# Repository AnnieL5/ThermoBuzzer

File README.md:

## ThermoBuzzer, a Thermosenser to Prevent Over Boiled Pots. 

### What it is
This device integrates a thermosensor, buzzer, and a button, and can make alarms when the temperature (the steam it detects) reaches a certain threshold. 

### Motivation / Inspiration / Problem

One Saturday afternoon my father left the stove, with the water heating up, for almost half an hour until the pot boiled dry and the fire alarm turned on, simply because he forgot the fact that the stove is still on. That moment inspired me to make a change - to build a device that could sense the temperature and alarm people that the burner is still active. 

### How to use it

1. Solder the electrical parts (see BOM) onto the PCB. Insert the PCB into the case and secure using m3 self-tapping screws

2. Insert the battery to start the machine. Slide in the lid and secure using a m3 self-tapping screw

3. Place it near the stoves. 

    Once the temperature continuously reaches 50 degrees (able to modify using a constant), ThermoBuzzer will beep continuously every five minutes until the button is clicked to ensure someone is there.

    Once the temperature reaches 70 degrees (able to modify using a constant), ThermoBuzzer will beep continuously right away until the button is clicked.

4. (Optional) To adjust the temperature threshold, take out the pcb from the case, modify amd reupload the program to the arduino pro mini.

### Code Example
Go checkout the example code in firmware/thermobuzzer.imo and upload it onto the arduino pro mini

For how to upload code onto arduino pro mini using arduino uno, check out 
https://www.instructables.com/How-to-Program-Arduino-Pro-Mini-Using-Arduino-UNO/

### Image of the entire cad / Finished product

### Image of the entire cad (with lid) / Finished product

### Image of the final PCB

### Image of the wiring schematic

## Zine page

## Demo Video

https://youtu.be/lv5Z6S4dAAs

## Product Design

### CAD dimensions
Side + top + base thickness: 2mm
supporting bar: r=4mm, h=4mm
Case height: 2mm base + 4mm supporting bar + 1.6mm board + 15.1mm battery height + 2mm flex + 2mm top

### Circuit Diagram 

### Sub-circuit Description
Diagrams from www.circuitbasics.com. 
#### Temperature sensor (NTC MF11) and Arduino

NTC MF11
The value of the resistor should be roughly equal to the resistance of the thermistor.

#### BME280
Reference links:

BME280
https://randomnerdtutorials.com/bme280-sensor-arduino-pressure-temperature-humidity/

https://docs.cirkitdesigner.com/component/3d8e6da8-841a-47a6-a1aa-0aa902c905e1/aht20bmp280

Code: https://randomnerdtutorials.com/bme280-sensor-arduino-pressure-temperature-humidity/

Arduino Library: adafruit bme280

It supports SPI or I2C communication

| BME280 |	Arduino |
|--|--|
|Vin | 	5V |
|GND |	GND |
|SCL |	A5 |
|SDA |	A4 |

| BME280 |	Arduino |
|--|--|
|SCK (SPI Clock)|	Pin 13|
|SDO (MISO)|	Pin 12|
|SDI (MOSI)|	Pin 11|
|CS (Chip Select)|	Pin 10|

#### Buzzer, Button and Arduino

## Requirements (Need future work)
| Req # | Requirements |
|---|---|
| 1.1 | The thermosensor shall be able to measure the temperature accurately for further actions|
| 1.2 | The thermosensor shall be able to beep when the temperature reaches a certain threshold |
| 1.3 | The button should be able to stop the buzzer from beeping |
| 1.4 | The temperature threshold should be adjustable by the user |

## Bill of Materials (BOM)
| Product name          | Product Description                          | Amount | Unit Price | Shipping Fee | Total Price | Link                                                                                                                                                                                                                                                                                                                                                                                                                                                                                                                                                                                                                                  |
| --------------------- | -------------------------------------------- | ------ | ---------- | ------------ | ----------- | ------------------------------------------------------------------------------------------------------------------------------------------------------------------------------------------------------------------------------------------------------------------------------------------------------------------------------------------------------------------------------------------------------------------------------------------------------------------------------------------------------------------------------------------------------------------------------------------------------------------------------------- |
| Arduino Pro Mini,      | ÊATMEGA328P 3.3V 8MHz                        | 1      | $6.14      |              | $6.14       | https://www.aliexpress.com/item/1005009384358010.html?spm=a2g0o.detail.0.0.3d69kxh4kxh4TT&mp=1&pdp_npi=6%40dis%21CAD%21CAD+12.34%21CAD+6.19%21%21CAD+6.19%21%21%21%402101e2b217772431183538792e7ffd%2112000048937356319%21ct%21CA%216218818596%21%211%210%21                                                                                                                                                                                                                                                                                                                                                                          |
| Temperature Sensor,    | AHT20+BMP280                                 | 1      | $4.59      |              | $4.59       | https://www.aliexpress.com/item/1005005982427374.html?spm=a2g0o.detail.0.0.91dbOMYjOMYjR3&mp=1&sourceType=570&pdp_npi=6%40dis%21CAD%21CAD+7.57%21CAD+4.59%21%21CAD+4.59%21%21%21%402101d6ff17773442520382830e94da%2112000035166631251%21ct%21CA%216218818596%21%211%210%21&pdp_ext_f=%7B%22cart2PdpParams%22%3A%7B%22sourceType%22%3A%22570%22%2C%22cartSource%22%3A%22main%22%7D%7D                                                                                                                                                                                                                                                  |
| Thermisor,             | 10PCS NTC ThermistorÊMF52 NTC-MF52AT         | 1      | 3.46       |              | $3.46       | https://www.aliexpress.com/item/1005007016386078.html?spm=a2g0o.detail.0.0.177fzTz7zTz79e&mp=1&pdp_npi=6%40dis%21CAD%21CAD+7.07%21CAD+3.46%21%21CAD+3.46%21%21%21%402101d6ff17773445233621202e94da%2112000039082044667%21ct%21CA%216218818596%21%211%210%21                                                                                                                                                                                                                                                                                                                                                                           |
| Passive Buzzer,        | 10PCS Passive Buzzer Kits 12085              | 1      | 2.79       |              | $2.79       | https://www.aliexpress.com/item/1005007038458518.html?spm=a2g0o.detail.0.0.291d6UQD6UQDcn&mp=1&sourceType=570&pdp_npi=6%40dis%21CAD%21CAD+7.56%21CAD+3.09%21%21CAD+3.09%21%21%21%402101d6ff17773446457813771e94da%2112000039180355191%21ct%21CA%216218818596%21%211%210%21&pdp_ext_f=%7B%22cart2PdpParams%22%3A%7B%22sourceType%22%3A%22570%22%2C%22cartSource%22%3A%22main%22%7D%7D                                                                                                                                                                                                                                                  |
| Buttons,               | 6\*6\*10mm 20pics                            | 1      | 2.29       |              | $2.29       | https://www.aliexpress.com/item/1005006046180384.html?spm=a2g0o.cart.0.0.31e138dackOqlz&mp=1&pdp_npi=6%40dis%21CAD%21CAD+2.29%21CAD+2.29%21%21CAD+2.29%21%21%21%402103119c17773470443845760e9623%2112000035472972539%21ct%21CA%216218818596%21%211%210%21                                                                                                                                                                                                                                                                                                                                                                             |
| AA Battery,            | 1                                            | NA     |            |              |             |
| THT Battery Holder    | 14500 Battery Box With Pins 1AA 1.5V         | 1      | 0.33       | 7.48         | $7.81       | https://www.aliexpress.com/item/1005005620966310.html?spm=a2g0o.cart.0.0.358a38dadNcuNR&mp=1&pdp_npi=6%40dis%21CAD%21CAD+0.38%21CAD+0.32%21%21CAD+0.32%21%21%21%402101eee917774109006605329ec0dc%2112000033776650718%21ct%21CA%216218818596%21%215%210%21                                                                                                                                                                                                                                                                                                                                                                             |
| Voltage Regulator,     | 0.8V-5V to 3V 3.3V 5V Boost Voltage Regulate | 1      | 3.85       |              | $3.85       | https://www.aliexpress.com/item/1005006167931077.html?spm=a2g0o.detail.0.0.4a7cjdtRjdtRpQ&mp=1&pdp_npi=6%40dis%21CAD%21CAD+3.96%21CAD+3.86%21%21CAD+3.86%21%21%21%402101d6ff17773444964128610e94da%2112000036084126229%21ct%21CA%216218818596%21%211%210%21                                                                                                                                                                                                                                                                                                                                                                           |
| m3 self-tapping screw, | ZONSANTA M3x50pc 5mm                         | 1      | 2.79       |              | $2.79       | https://www.aliexpress.com/item/4000982209705.html?spm=a2g0o.productlist.main.2.5e0a5049GO2c6k&algo_pvid=d9d1041d-5b82-4d1d-adb8-2c50ae22e721&algo_exp_id=d9d1041d-5b82-4d1d-adb8-2c50ae22e721-1&pdp_ext_f=%7B%22order%22%3A%2214058%22%2C%22eval%22%3A%221%22%2C%22fromPage%22%3A%22search%22%7D&pdp_npi=6%40dis%21CAD%212.04%211.99%21%21%211.46%211.42%21%40210328d417774091351247794e1c13%2110000013191635027%21sea%21CA%216218818596%21X%211%210%21n_tag%3A-29919%3Bd%3A26a99932%3Bm03_new_user%3A-29895&curPageLogUid=Y5TAugc4ns7L&utparam-url=scene%3Asearch%7Cquery_from%3A%7Cx_object_id%3A4000982209705%7C_p_origin_prod%3A |
| resistor,              | 100k                                         | 1      | 0          |              | $0.00       |                                                                                                                                                                                                                                                                                                                                                                                                                                                                                                                                                                                                                                       |
| resistor,              | 10k                                          | 1      | 0          |              | $0.00       |                                                                                                                                                                                                                                                                                                                                                                                                                                                                                                                                                                                                                                       |
| head pins,             | 5 male 5 female                              | 1      | 5.19       |              | $5.19       | https://www.aliexpress.com/item/1005007235591794.html?spm=a2g0o.cart.0.0.31e138dackOqlz&mp=1&sourceType=570&pdp_npi=6%40dis%21CAD%21CAD+16.72%21CAD+5.19%21%21CAD+5.19%21%21%21%402103119c17773470443845760e9623%2112000039908542823%21ct%21CA%216218818596%21%211%210%21&pdp_ext_f=%7B%22cart2PdpParams%22%3A%7B%22sourceType%22%3A%22570%22%2C%22cartSource%22%3A%22main%22%7D%7D                                                                                                                                                                                                                                                   |
| Total                 |                                              |        |            |              | $38.91      |                                                                                                                                                                                                                                                                                                                                                                                                                                                                                                                                                                                                                                       |

### Thanks for checking it out!
Any questions or thoughts, feel free to reach out to atianyi.liang@gmail.com.

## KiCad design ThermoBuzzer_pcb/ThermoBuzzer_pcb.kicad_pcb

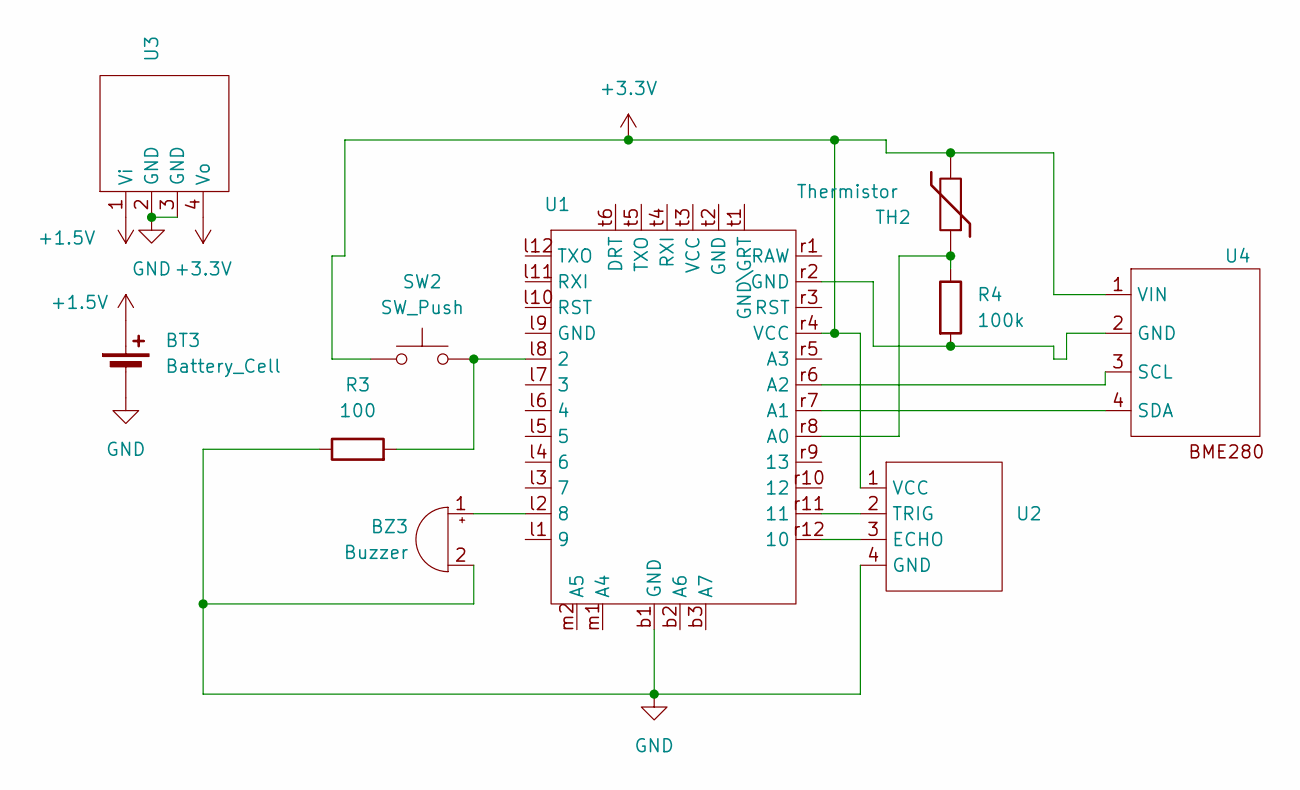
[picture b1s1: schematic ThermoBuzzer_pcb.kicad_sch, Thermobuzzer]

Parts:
BT3: Battery_Cell; BatteryHolder_Keystone_2460_1xAA
BZ3: Buzzer; Buzzer_12x9.5RM7.6
R3: 100; R_Axial_DIN0207_L6.3mm_D2.5mm_P7.62mm_Horizontal
R4: 100k; R_Axial_DIN0207_L6.3mm_D2.5mm_P7.62mm_Horizontal
SW2: SW_Push; SW_PUSH_6mm
TH2: Thermistor; R_Axial_DIN0207_L6.3mm_D2.5mm_P7.62mm_Horizontal
U1: arduino_pro_mini_new
U2: Ultrasonic Sensor HC-SR04
U3: ND0205MA Voltage Regulator
U4: AHT20+BMP280

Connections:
+1.5V: BT3.1 (+), U3.1 (Vi)
+3.3V: SW2.1, TH2.2, U1.r4 (VCC), U2.1 (VCC), U3.4 (Vo), U4.1 (VIN)
GND: BT3.2 (-), BZ3.2 (-), R3.1, U1.b1 (GND), U2.4 (GND), U3.2 (GND), U3.3 (GND)
unnamed: BZ3.1 (+), U1.l2 (8)
unnamed: R3.2, SW2.2, U1.l8 (2)
unnamed: U1.r12 (10), U2.3 (ECHO)
unnamed: U1.r11 (11), U2.2 (TRIG)
unnamed: R4.1, TH2.1, U1.r8 (A0)
unnamed: U1.r7 (A1), U4.4 (SDA)
unnamed: U1.r6 (A2), U4.3 (SCL)
unnamed: R4.2, U1.r2 (GND), U4.2 (GND)

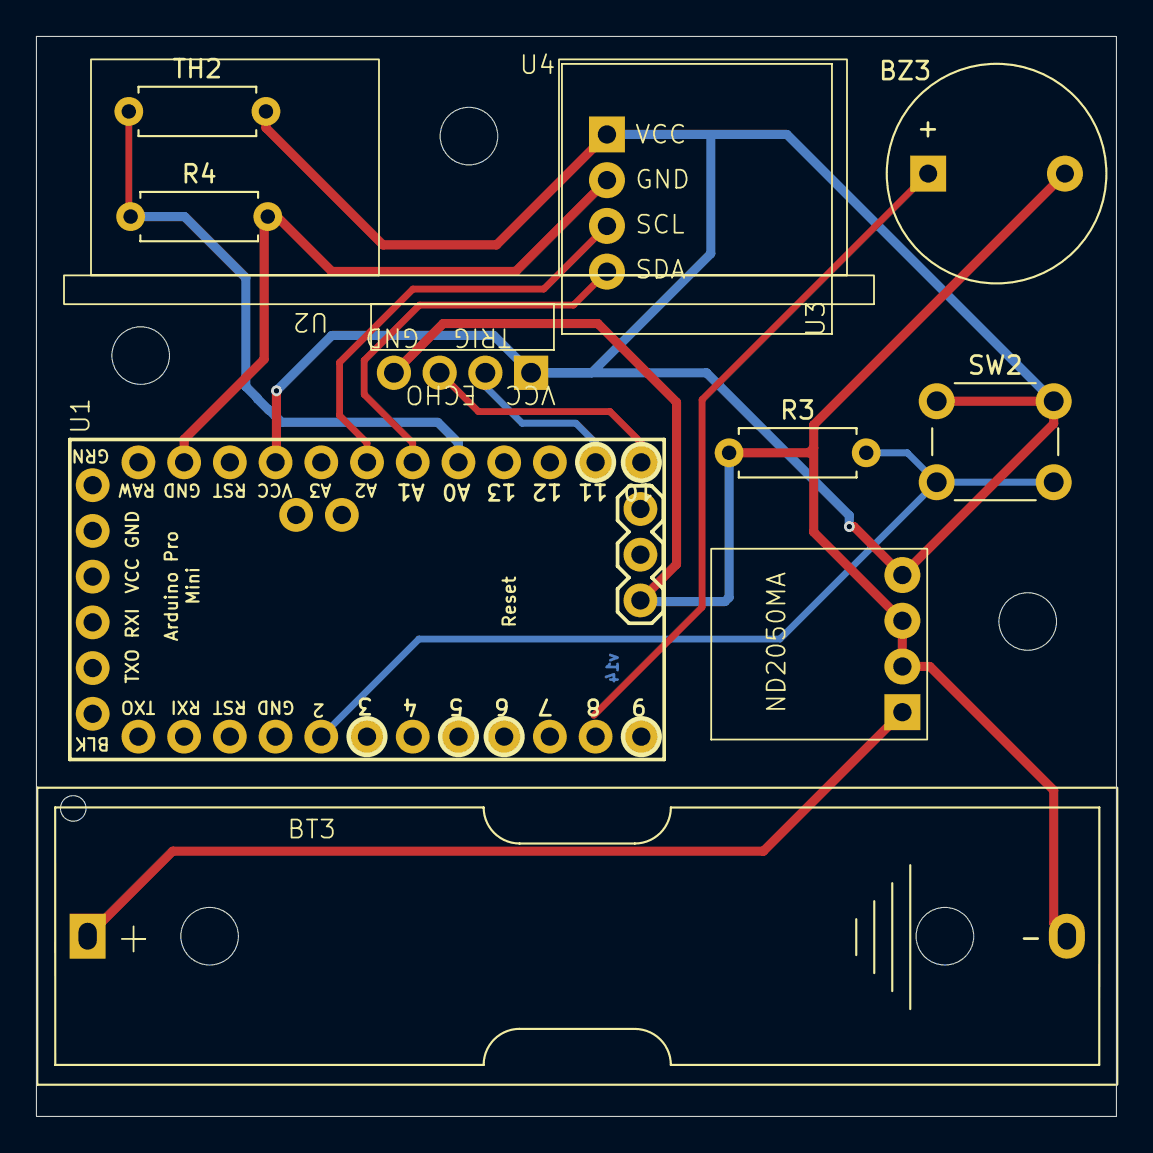
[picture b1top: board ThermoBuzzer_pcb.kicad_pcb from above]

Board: 2 copper layers, 60.0 x 60.0 mm, 10 parts (0 on the bottom side), 11 nets.

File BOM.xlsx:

BOM
Part Name | Type | Reference Designator | Quantity | Price | Link | Price | Notes
Temperature Sensor | NTC MF11, AHT20+BMP280 |  | 1 | 2.19 | AHT20+BMP280 Temperature Humidity Air Pressure Module High-precision Digital Te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 |  | https://www.aliexpress.com/ssr/300000512/BundleDeals2?spm=a2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 | https://www.amazon.ca/ANALOG-DEVICES-TMP36-Temperature-Senso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
Active Buzzer | 5V |  | 1 | 3.99 | https://www.aliexpress.com/w/wholesale-active-buzzer.html?g=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
Button |  |  | 1 | NA | https://www.aliexpress.com/w/wholesale-button-electronics.ht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
Resistor
Capacitor |  |  | 1 |  | https://www.aliexpress.com/w/wholesale-capacitor.html?g=y&Se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
Arduino | Arduino Nano (type) |  | 1 | 2.6 | https://www.aliexpress.com/item/1005004904865598.html?spm=a2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
 | Arduino pro mini |  |  | 6.19 | 1PCS Pro mini Atmega328 Pro Mini 328 Mini ATMEGA328P 3.3V 8MHz 5V 16Mhz for Ard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
Battery | 9v dc |  |  | 9.98 | https://www.amazon.ca/Duracell-Coppertop-Long-lasting-All-Pu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
Battery socket
Boost voltage regulator |  |  |  | 3.3 | Mini 0.8V-5V to 3V 3.3V 5V Boost Voltage Regulate Board Low-Power-Consumption H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
Product name | Product Description | Amount | Unit Price | Shipping Fee | Total Price | Link
Arduino Pro Mini | ATMEGA328P 3.3V 8MHz | 1 | 6.14 |  | 6.14 | https://www.aliexpress.com/item/1005009384358010.html?spm=a2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
Temperature Sensor | AHT20+BMP280 | 1 | 4.59 |  | 4.59 | https://www.aliexpress.com/item/1005005982427374.html?spm=a2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
Thermisor | 10PCS NTC Thermistor MF52 NTC-MF52AT | 1 | 3.46 |  | 3.46 | https://www.aliexpress.com/item/1005007016386078.html?spm=a2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
Passive Buzzer | 10PCS Passive Buzzer Kits 12085 | 1 | 2.79 |  | 2.79 | https://www.aliexpress.com/item/1005007038458518.html?spm=a2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
Buttons | 6*6*10mm 20pics | 1 | 2.29 |  | 2.29 | https://www.aliexpress.com/item/1005006046180384.html?spm=a2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
AA Battery |  | 1 | NA
THT Battery Holder | 14500 Battery Box With Pins 1AA 1.5V | 1 | 0.33 | 7.48 | 7.8100000000000005 | https://www.aliexpress.com/item/1005005620966310.html?spm=a2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
Voltage Regulator | 0.8V-5V to 3V 3.3V 5V Boost Voltage Regulate | 1 | 3.85 |  | 3.85 | https://www.aliexpress.com/item/1005006167931077.html?spm=a2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
 |  |  |  |  | 0
 |  |  |  |  | 0
m3 self-tapping screw | ZONSANTA M3x50pc 5mm | 1 | 2.79 |  | 2.79 | https://www.aliexpress.com/item/4000982209705.html?spm=a2g0o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
resistor | 100k | 1 | 0 |  | 0
resistor | 10k | 1 | 0 |  | 0
head pins | 5 male 5 female | 1 | 5.19 |  | 5.19 | https://www.aliexpress.com/item/1005007235591794.html?spm=a2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
Total |  |  |  |  | 38.909999999999997
GarageGuarde
Ultrasonic sensor | HC-SR04 3.3-5VNew version | 1 | 2.71 |  | 2.71 | https://www.aliexpress.com/item/1005005467178145.html?spm=a2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
Passive Buzzer | 10PCS Passive Buzzer Kits 12085 | 1 | 0 |  | 0
Arduino Pro Mini | ATMEGA328P 3.3V 8MHz | 1 | 6.14 |  | 6.14 | https://www.aliexpress.com/item/1005009384358010.html?spm=a2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
AA Battery |  | 1 | NA
THT Battery Holder | 14500 Battery Box With Pins 1AA 1.5V | 1 | 0.33 | NA | 0.33 | https://www.aliexpress.com/item/1005005620966310.html?spm=a2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
Voltage Regulator | 0.8V-5V to 3V 3.3V 5V Boost Voltage Regulate | 1 | 3.85 |  | 3.85 | https://www.aliexpress.com/item/1005006167931077.html?spm=a2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
m3 self-tapping screw | ZONSANTA M3x50pc 5mm | 1 | 0 |  | 0 | https://www.aliexpress.com/item/4000982209705.html?spm=a2g0o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
head pins | 5 male 5 female | 1 | 0 |  | 0 | https://www.aliexpress.com/item/1005007235591794.html?spm=a2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
 |  |  |  |  | 51.94

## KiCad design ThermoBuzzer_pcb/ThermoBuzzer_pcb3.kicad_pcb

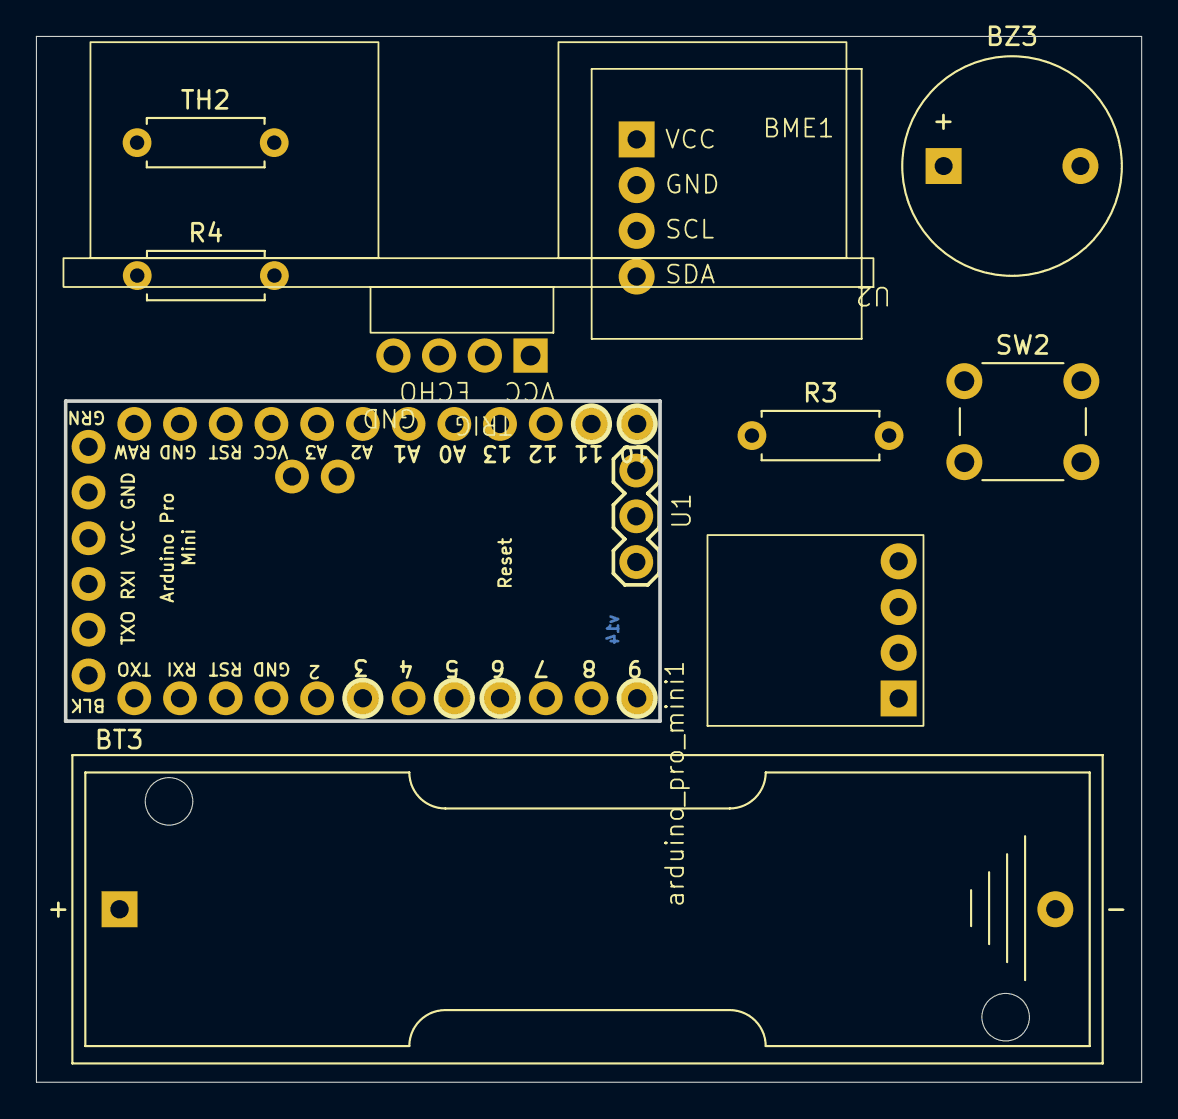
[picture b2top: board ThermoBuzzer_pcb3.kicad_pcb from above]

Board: 2 copper layers, 61.2 x 57.9 mm, 10 parts (0 on the bottom side), 10 nets, no tracks yet.

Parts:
BME1: AHT20+BMP280
BT3: Battery_Cell; BatteryHolder_Keystone_2460_1xAA
BZ3: Buzzer; Buzzer_12x9.5RM7.6
R3: 100; R_Axial_DIN0207_L6.3mm_D2.5mm_P7.62mm_Horizontal
R4: 100k; R_Axial_DIN0207_L6.3mm_D2.5mm_P7.62mm_Horizontal
SW2: SW_Push; SW_PUSH_6mm
TH2: Thermistor; R_Axial_DIN0207_L6.3mm_D2.5mm_P7.62mm_Horizontal
U1: ND0205MA Voltage Regulator
U2: Ultrasonic Sensor HC-SR04
arduino_pro_mini1: arduino_pro_mini_new

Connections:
+1.5V: BT3.1 (+), U1.1 (Vi)
+3.3V: BME1.1 (VIN), SW2.1, TH2.1, U1.4 (Vo), U2.1 (VCC), arduino_pro_mini1.r4 (VCC)
GND: BME1.2 (GND), BT3.2 (-), BZ3.2 (-), R3.1, R4.2, U1.2 (GND), U1.3 (GND), U2.4 (GND), arduino_pro_mini1.b1 (GND)
unnamed: BME1.3 (SCL), arduino_pro_mini1.r6 (A2)
unnamed: BME1.4 (SDA), arduino_pro_mini1.r7 (A1)
unnamed: BZ3.1 (+), arduino_pro_mini1.l2 (8)
unnamed: U2.3 (ECHO), arduino_pro_mini1.r12 (10)
unnamed: U2.2 (TRIG), arduino_pro_mini1.r11 (11)
unnamed: R3.2, SW2.2, arduino_pro_mini1.l8 (2)
unnamed: R4.1, TH2.2, arduino_pro_mini1.r8 (A0)

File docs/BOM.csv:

Product name,Product Description,Amount,Unit Price,Shipping Fee,Total Price,LinkArduino Pro Mini,ÊATMEGA328P 3.3V 8MHz,1,$6.14,,$6.14,https://www.aliexpress.com/item/1005009384358010.html?spm=a2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Temperature Sensor,AHT20+BMP280,1,$4.59,,$4.59,https://www.aliexpress.com/item/1005005982427374.html?spm=a2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Thermisor,10PCS NTC ThermistorÊMF52 NTC-MF52AT,1,3.46,,$3.46,https://www.aliexpress.com/item/1005007016386078.html?spm=a2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Passive Buzzer,10PCS Passive Buzzer Kits 12085,1,2.79,,$2.79,https://www.aliexpress.com/item/1005007038458518.html?spm=a2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Buttons,6*6*10mm 20pics,1,2.29,,$2.29,https://www.aliexpress.com/item/1005006046180384.html?spm=a2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,,,,,,,,,,,,AA Battery,,1,NA,,,THT Battery Holder,14500 Battery Box With Pins 1AA 1.5V,1,0.33,7.48,$7.81,https://www.aliexpress.com/item/1005005620966310.html?spm=a2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Voltage Regulator,0.8V-5V to 3V 3.3V 5V Boost Voltage Regulate,1,3.85,,$3.85,https://www.aliexpress.com/item/1005006167931077.html?spm=a2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,,,,,$0.00,,,,,,$0.00,m3 self-tapping screw,ZONSANTA M3x50pc 5mm,1,2.79,,$2.79,https://www.aliexpress.com/item/4000982209705.html?spm=a2g0o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resistor,100k,1,0,,$0.00,resistor,10k,1,0,,$0.00,head pins,5 male 5 female,1,5.19,,$5.19,https://www.aliexpress.com/item/1005007235591794.html?spm=a2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,,,,,,Total,,,,,$38.91,

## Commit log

2025-08-26 Add circuit diagram
2025-08-29 modify diagram
2026-03-21 Update readme, create BOM and started PCB
2026-03-22 Further work on Schematics + parts
2026-03-24 Finalize arduino + temperature
2026-04-05 april 4 schematic + footprints
2026-04-06 april 5 update
2026-04-16 4.15
2026-04-17 4.16
2026-04-18 4.17
2026-04-19 4.18
2026-04-21 4.20
2026-04-22 4.21
2026-04-23 4.22
2026-04-24 4.23
2026-04-25 4.24
2026-04-28 4.27
2026-04-29 4.28
2026-04-29 4.29
2026-05-01 4.30
2026-05-06 5.5.2
2026-05-06 rename file
2026-05-07 5.6.2
2026-05-11 5.11
2026-05-14 5.13
2026-05-14 create pcb folder
2026-05-27 5.26
2026-05-29 5.28
2026-05-29 organize folders
2026-05-29 minor
2026-06-18 6.17
2026-06-21 6.20
2026-06-21 update bom
2026-06-21 maybe this will work?
2026-06-21 maybe this?
